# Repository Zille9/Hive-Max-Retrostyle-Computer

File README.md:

# Hive-Max-Retrostyle-Computer
umfangreich erweiterter Hive-Retrostyle-Computer

Folgende Änderungen wurden durchgeführt:
- 2xJoystick Ports (wie Mini-Joystickkarte)
- Bellatrix-Ram-Erweiterung integriert (für Emulatoren)
- Umschaltung Soundquelle von Administra nach Bellatrix (für Emulatoren)
- zusätzlicher Latchbaustein für die Aktivierung/Deaktivierung zusätzlicher Funktionen
- Portsperren am Bellatrix VGA-Ausgang, um die Ports für eigene Erweiterungen zu nutzen (andere Grafikhardware, CP/M-Emulation usw.)
- Möglichkeit der Anbindung des Micromite an den Hive
- Expansionsport als C64 Modulport ausgebildet für Hardware-Steckmodule
- automatische EEPROM-Umschaltung durch die Steckmodule über Adressumschaltung
- Latch-Diagnoseanschluss für den Zusatzlatch zur Funktionskontrolle

Für weitere Informationen siehe auch https://hive-project.de

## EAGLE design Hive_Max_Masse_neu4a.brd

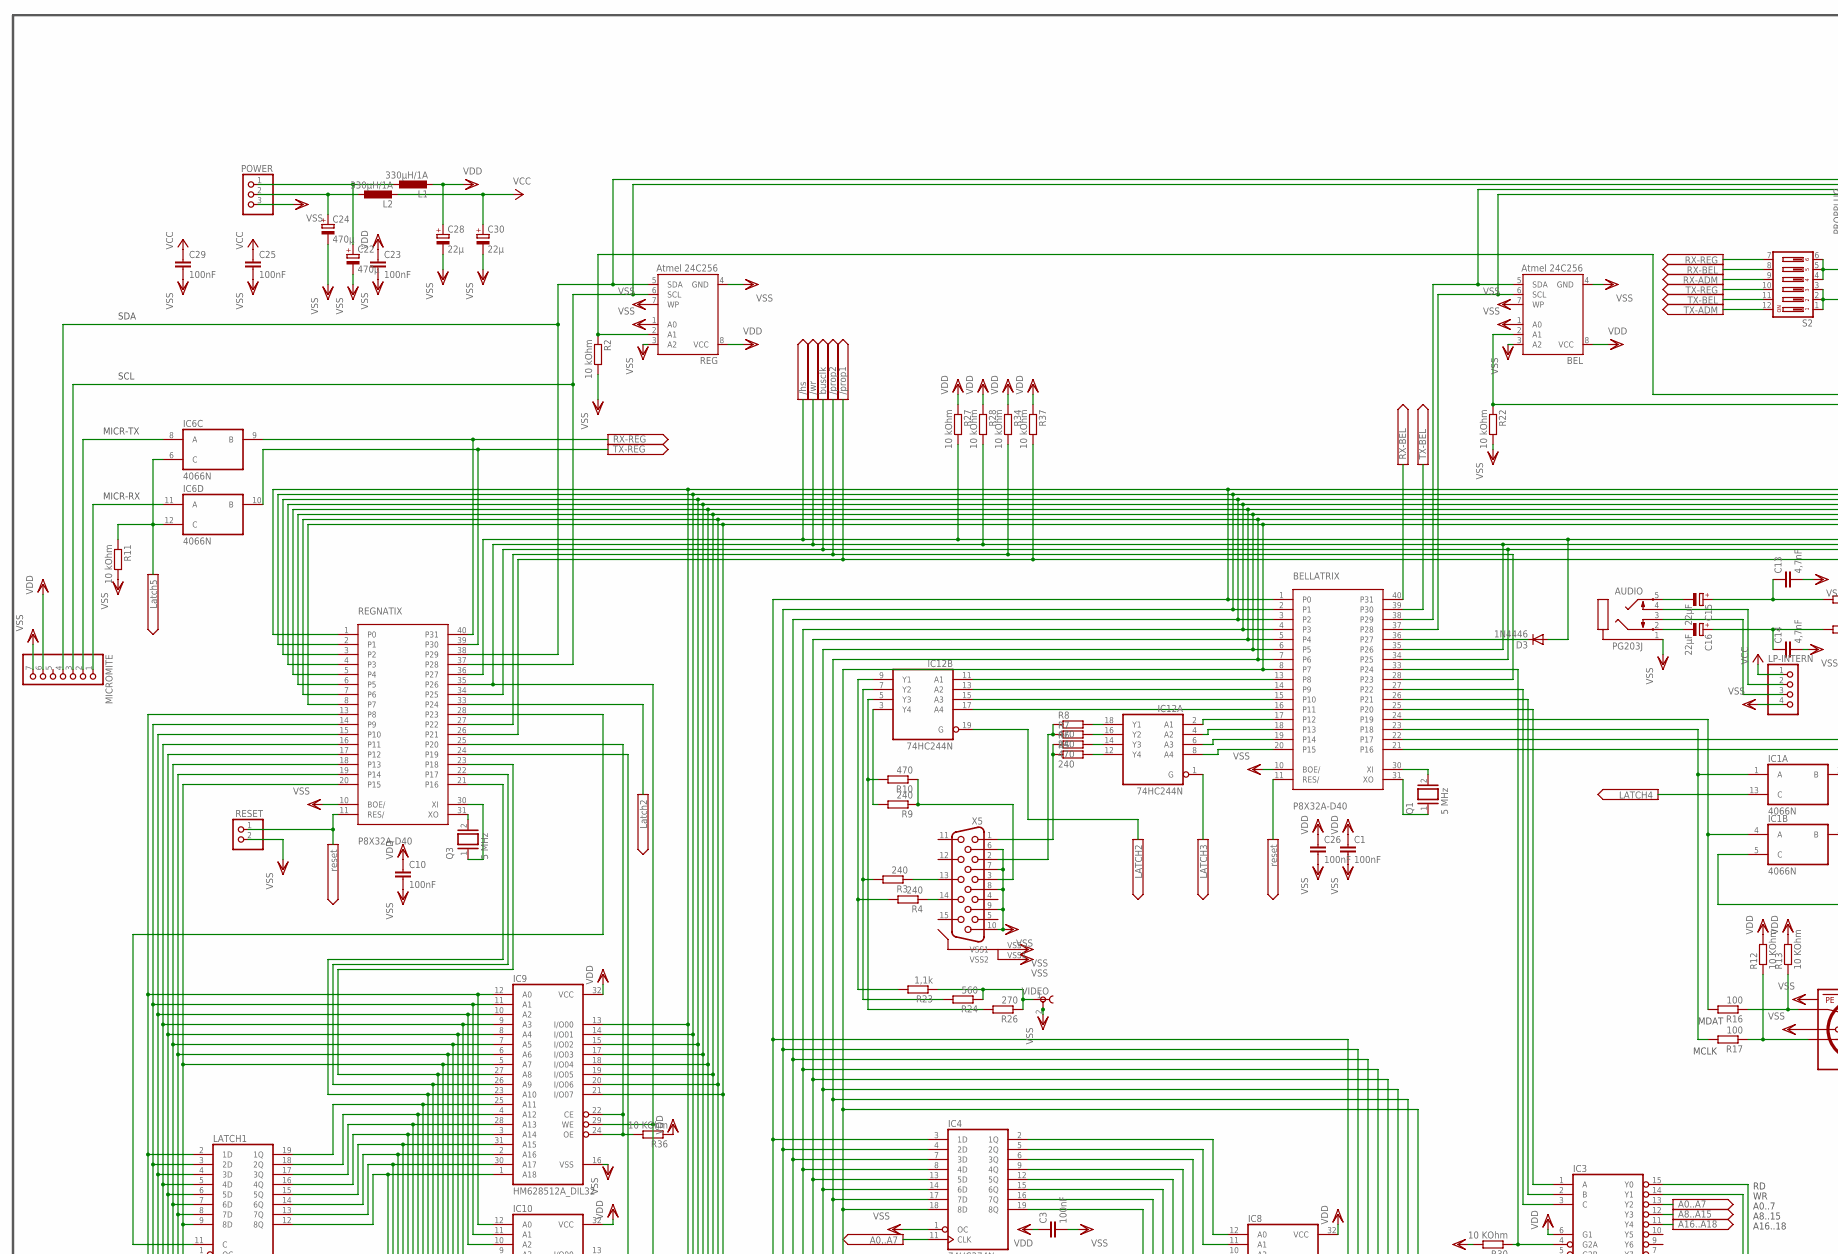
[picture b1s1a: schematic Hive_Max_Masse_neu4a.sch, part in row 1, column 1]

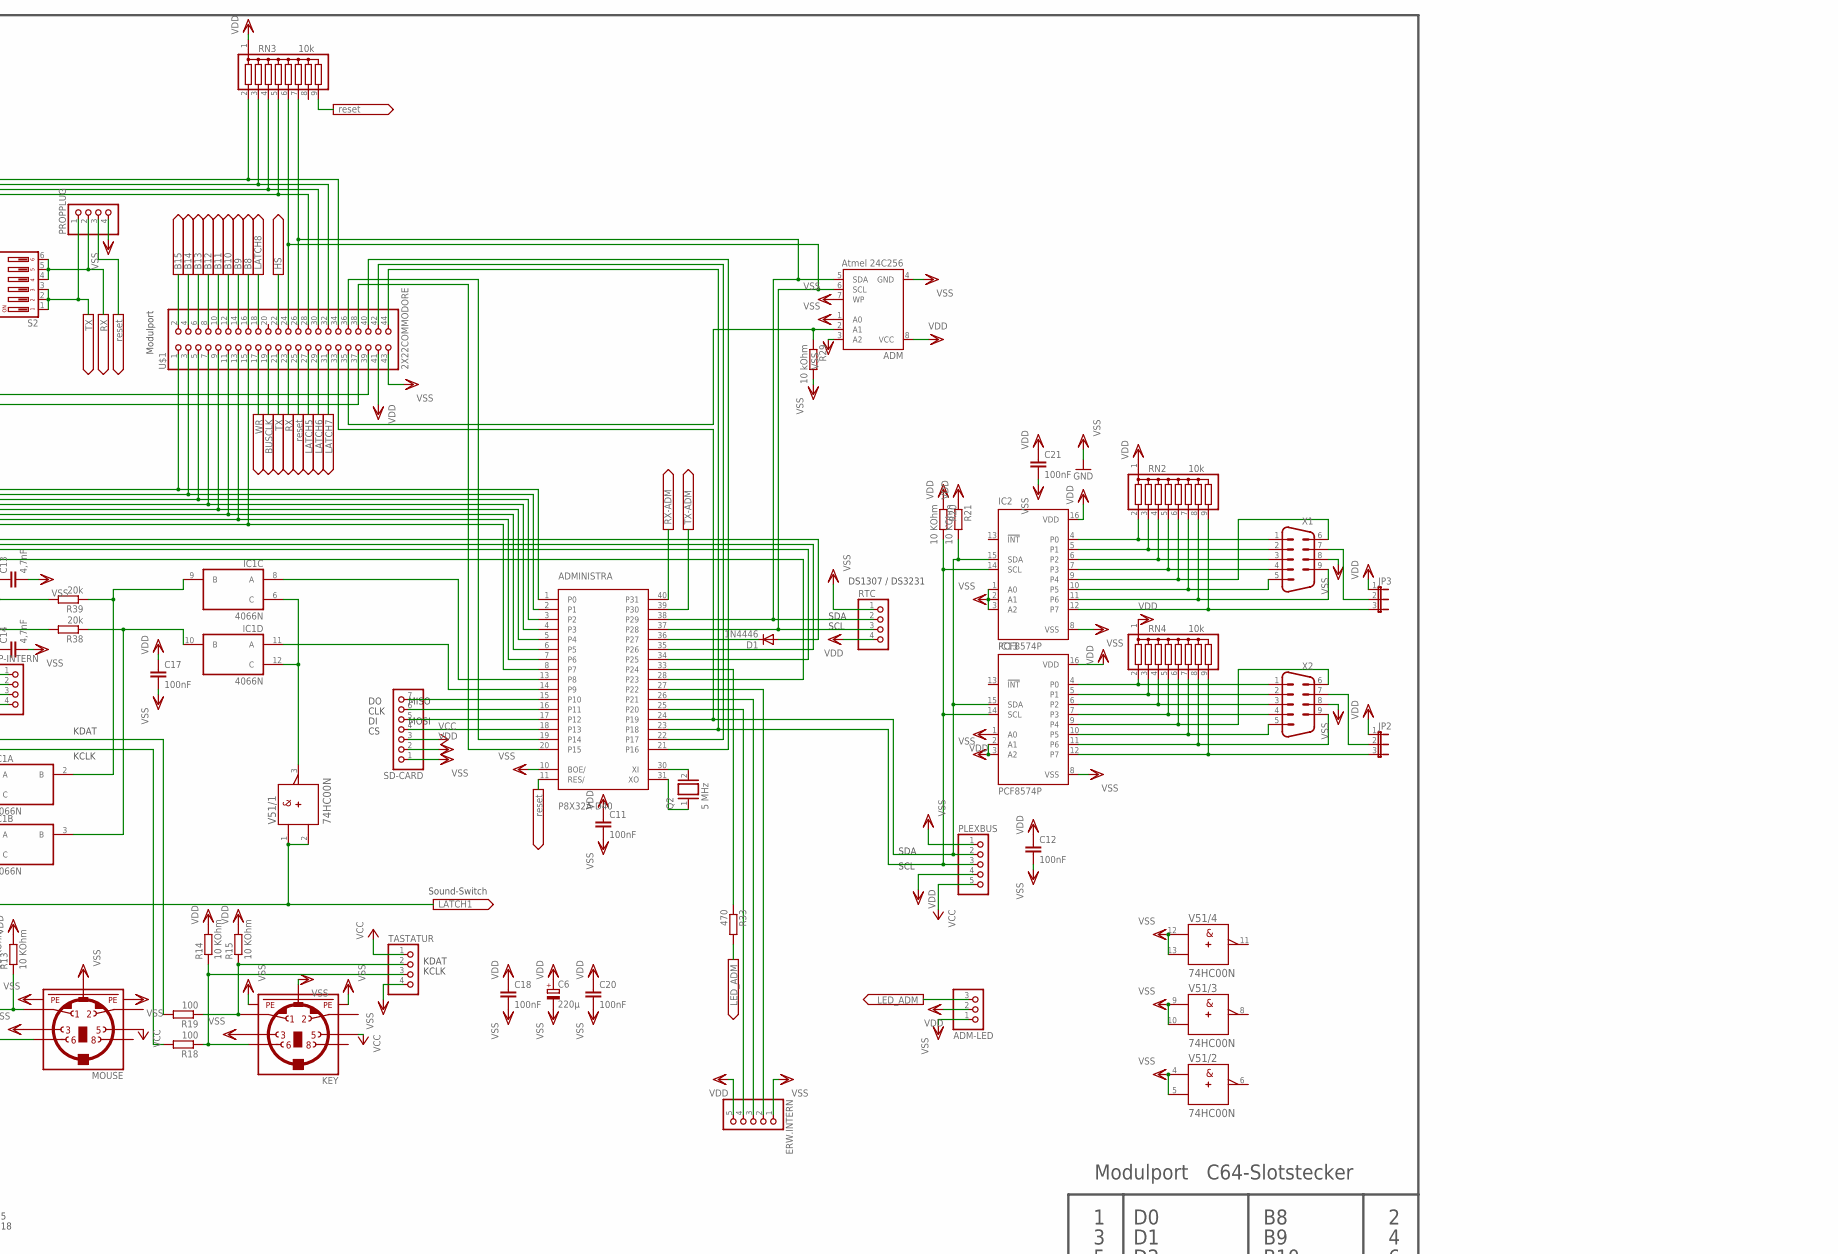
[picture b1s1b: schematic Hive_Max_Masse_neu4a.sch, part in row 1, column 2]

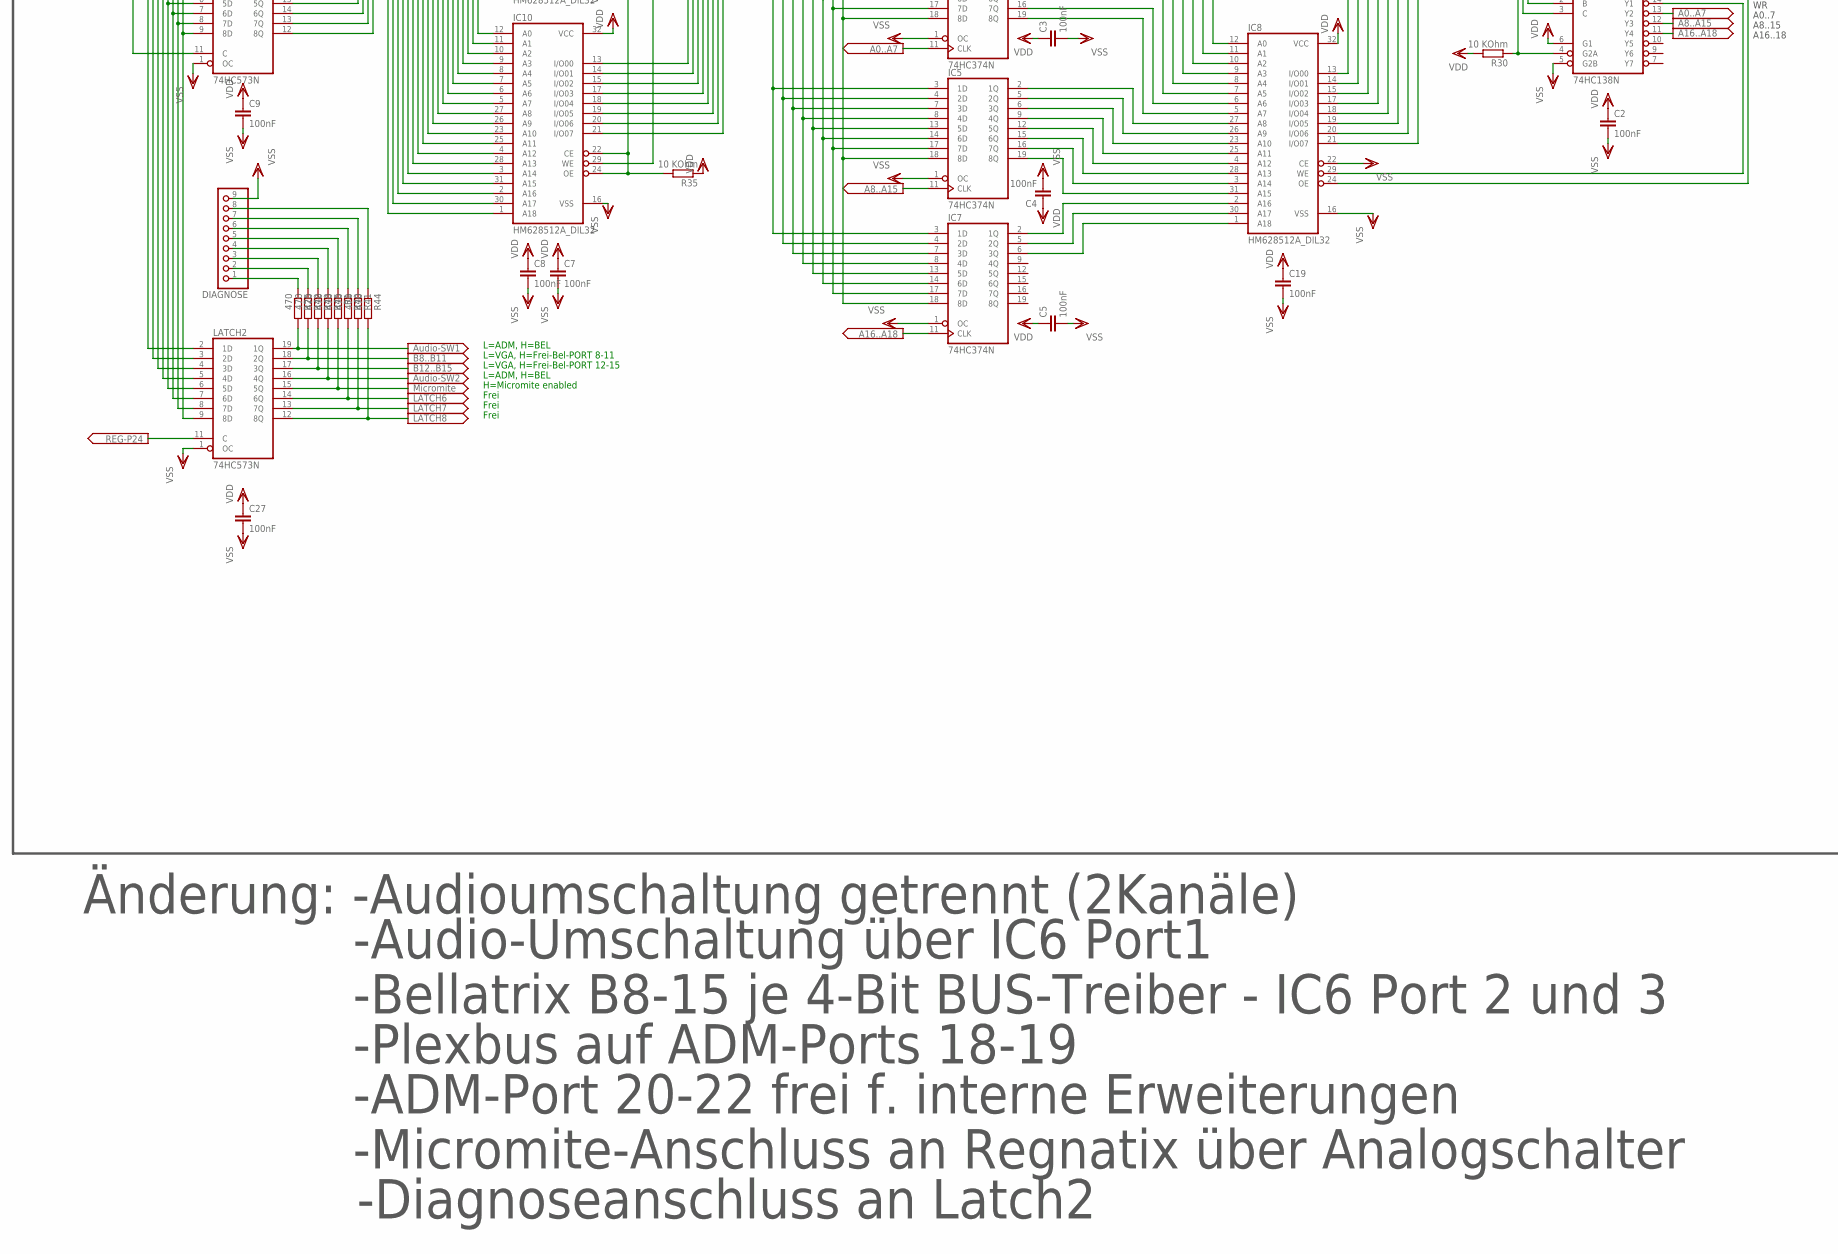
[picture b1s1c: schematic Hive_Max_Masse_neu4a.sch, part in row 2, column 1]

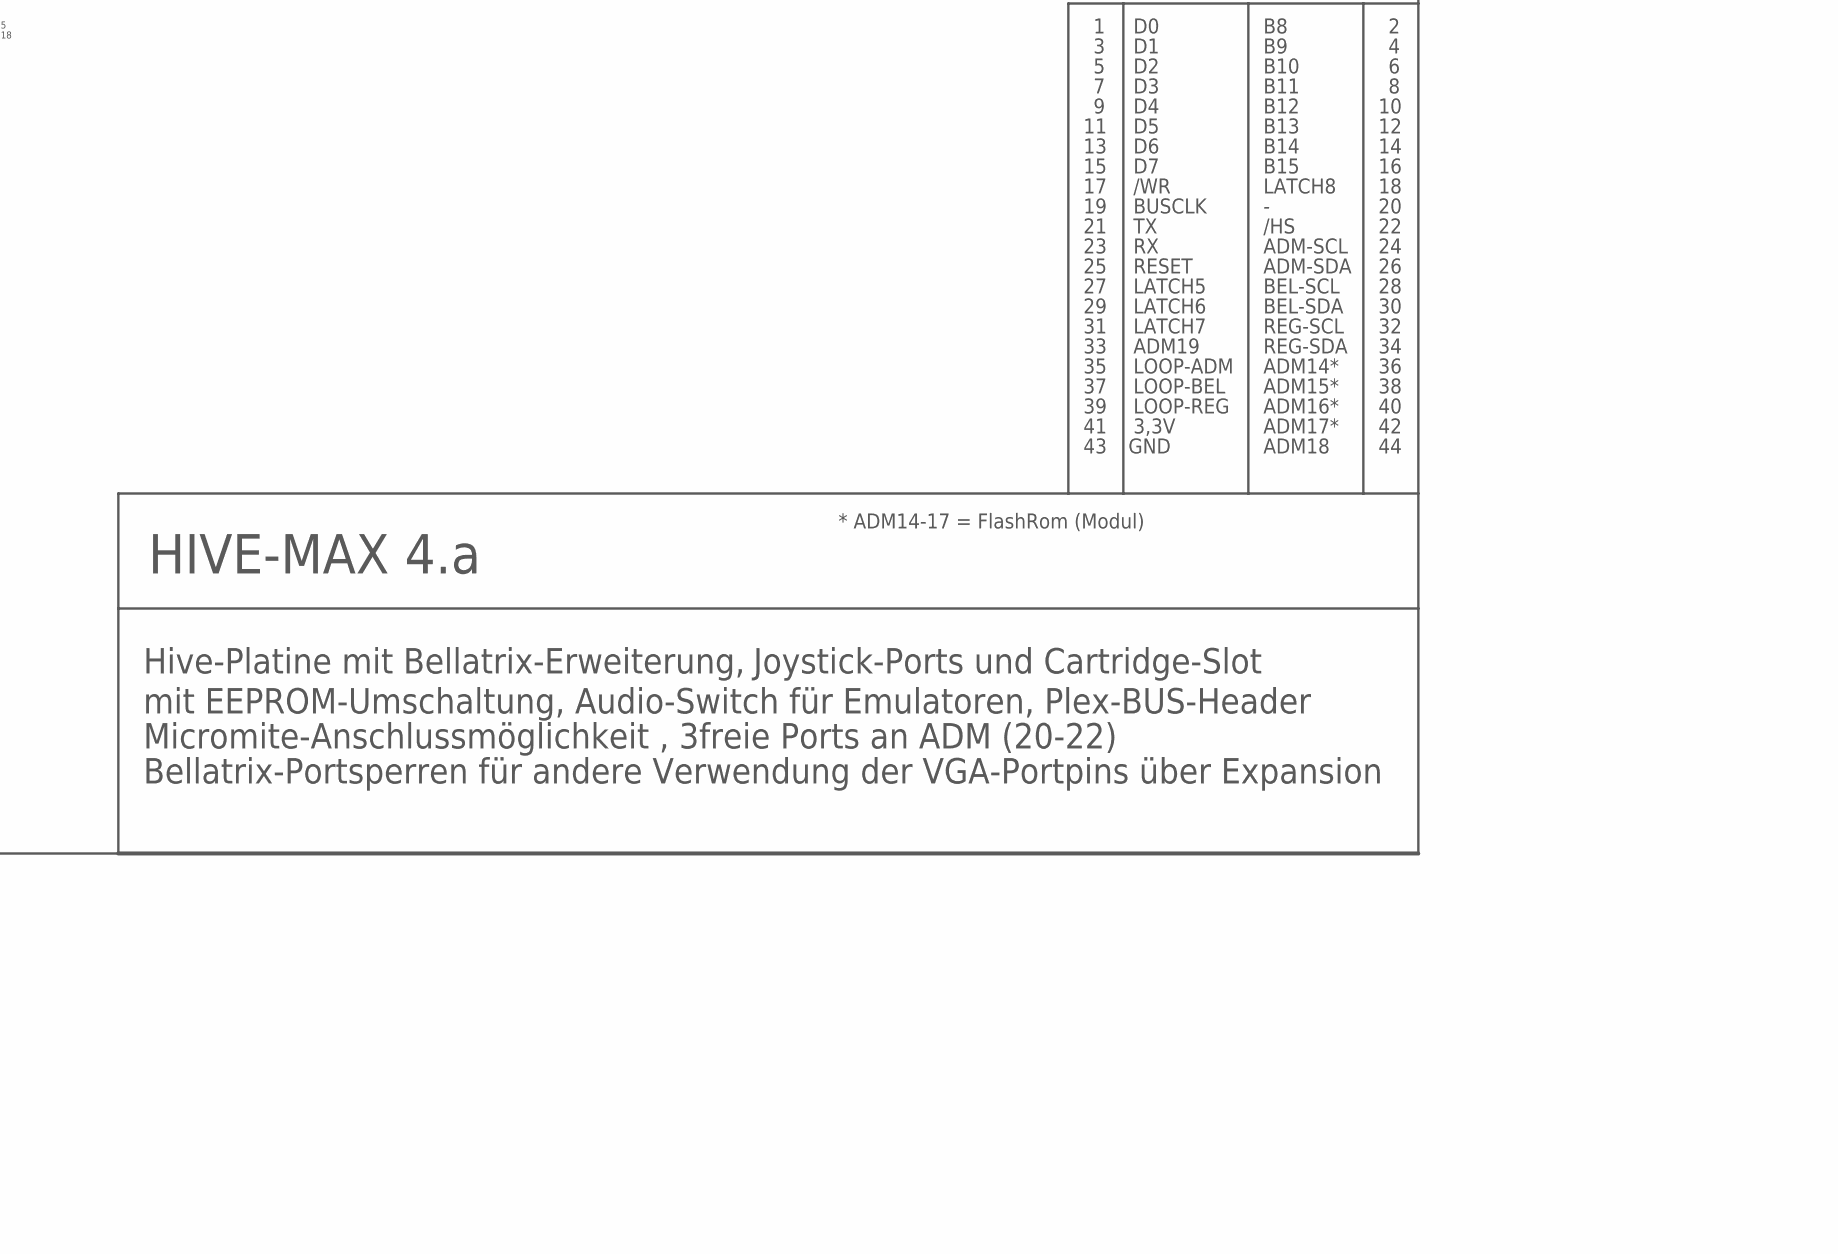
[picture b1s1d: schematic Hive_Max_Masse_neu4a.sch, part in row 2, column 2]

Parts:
ADM: Atmel 24C256; DIL08
ADM-LED: PINHD-1X3; 1X03
ADMINISTRA: P8X32A-D40
AUDIO: PG203J
BEL: Atmel 24C256; DIL08
BELLATRIX: P8X32A-D40
C1, C2, C3, C4, C5, C7, C8, C9, C10, C11, C12, C17, C18, C19, C20, C21, C23, C25, C26, C27, C29: 100nF; C025-030X050
C6: 220µ; E5-8,5
C13, C14: 4,7nF; C025-030X050
C15, C16: 22µF; E2-5
C22, C24: 470µ; E5-8,5
C28, C30: 22µ; E2-5
D1, D3: 1N4446; DO35-10
DIAGNOSE: PINHD-1X9; 1X09
ERW.INTERN: PINHD-1X5; 1X05
IC1, IC6: 4066N; DIL14
IC2, IC13: PCF8574P; DIL16
IC3: 74HC138N; DIL16
IC4, IC5, IC7: 74HC374N; DIL20
IC8, IC9, IC10: HM628512A_DIL32; DIL32
IC12: 74HC244N; DIL20
JP2, JP3: JP2E; JP2
KEY: MINI_DIN_6; M_DIN6
L1, L2: 330µH/1A; 6000-XXXX-RC
LATCH1, LATCH2: 74HC573N; DIL20
LP-INTERN: PINHD-1X4; 1X04
MICROMITE: PINHD-1X7; 1X07
MOUSE: MINI_DIN_6; M_DIN6
PLEXBUS: PINHD-1X5; 1X05
POWER: PINHD-1X3; 1X03
PROPPLUG: PINHD-1X4/90; 1X04/90
Q1, Q2, Q3: 5 MHz; QS
R1, R6, R8, R10, R25, R33, R40, R41, R42, R43, R44, R45: 470; 0204V
R2, R11, R22, R27, R28, R29, R34, R37: 10 kOhm; 0204V
R3, R4, R5, R7, R9: 240; 0204V
R12, R13, R14, R15, R20, R21, R30, R35, R36: 10 KOhm; 0204V
R16, R17, R18, R19: 100; 0204V
R23: 1,1k; 0204V
R24: 560; 0204V
R26: 270; 0204V
R38, R39: 20k; 0204V
REG: Atmel 24C256; DIL08
REGNATIX: P8X32A-D40
RESET: PINHD-1X2; 1X02
RN2, RN3, RN4: 10k; SIL9
RTC: PINHD-1X4; 1X04
S2: DA06; DA-06
SD-CARD: PINHD-1X7; 1X07
TASTATUR: PINHD-1X4; 1X04
U$1: 2X22COMMODORE; 2X22-COMMODORE
V51: 74HC00N; DIL14
VIDEO: CINCHFEM; TOBU3
X1, X2: M09HP
X5: HF15H; HDF15H

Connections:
/HS: D1.A, D3.A, R27.2, REGNATIX.36 (P27), U$1.22
A0: IC9.12 (A0), IC10.12 (A0), LATCH1.2 (1D), LATCH2.2 (1D), REGNATIX.13 (P8)
A0..A7: IC3.13 (Y2), IC4.11 (CLK)
A1: IC9.11 (A1), IC10.11 (A1), LATCH1.3 (2D), LATCH2.3 (2D), REGNATIX.14 (P9)
A2: IC9.10 (A2), IC10.10 (A2), LATCH1.4 (3D), LATCH2.4 (3D), REGNATIX.15 (P10)
A3: IC9.9 (A3), IC10.9 (A3), LATCH1.5 (4D), LATCH2.5 (4D), REGNATIX.16 (P11)
A4: IC9.8 (A4), IC10.8 (A4), LATCH1.6 (5D), LATCH2.6 (5D), REGNATIX.17 (P12)
A5: IC9.7 (A5), IC10.7 (A5), LATCH1.7 (6D), LATCH2.7 (6D), REGNATIX.18 (P13)
A6: IC9.6 (A6), IC10.6 (A6), LATCH1.8 (7D), LATCH2.8 (7D), REGNATIX.19 (P14)
A7: IC9.5 (A7), IC10.5 (A7), LATCH1.9 (8D), LATCH2.9 (8D), REGNATIX.20 (P15)
A8: IC9.23 (A10), IC10.23 (A10), REGNATIX.21 (P16)
A8..A15: IC3.12 (Y3), IC5.11 (CLK)
A9: IC9.26 (A9), IC10.26 (A9), REGNATIX.22 (P17)
A10: IC9.27 (A8), IC10.27 (A8), REGNATIX.23 (P18)
A16..A18: IC3.11 (Y4), IC7.11 (CLK)
ADM14: ADMINISTRA.19 (P14), U$1.36
ADM15: ADMINISTRA.20 (P15), U$1.38
ADM16: ADMINISTRA.21 (P16), U$1.40
ADM17: ADMINISTRA.22 (P17), U$1.42
ADM18: ADMINISTRA.23 (P18), IC2.14 (SCL), IC13.14 (SCL), PLEXBUS.3, R20.2, U$1.44
ADM19: ADMINISTRA.24 (P19), IC2.15 (SDA), IC13.15 (SDA), PLEXBUS.2, R21.2, U$1.33
ADM20: ADMINISTRA.25 (P20), ERW.INTERN.4
ADM21: ADMINISTRA.26 (P21), ERW.INTERN.3
ADM22: ADMINISTRA.27 (P22), ERW.INTERN.2
ADM-SCL: ADM.6 (SCL), ADMINISTRA.37 (P28), RN3.6, RTC.3, U$1.24
ADM-SDA: ADM.5 (SDA), ADMINISTRA.38 (P29), RN3.7, RTC.2, U$1.26
B8: BELLATRIX.13 (P8), IC12.11 (A1), U$1.16
B9: BELLATRIX.14 (P9), IC12.13 (A2), U$1.14
B10: BELLATRIX.15 (P10), IC12.15 (A3), U$1.12
B11: BELLATRIX.16 (P11), IC12.17 (A4), U$1.10
B12: BELLATRIX.17 (P12), IC12.2 (A1), U$1.8
B13: BELLATRIX.18 (P13), IC12.4 (A2), U$1.6
B14: BELLATRIX.19 (P14), IC12.6 (A3), U$1.4
B15: BELLATRIX.20 (P15), IC12.8 (A4), U$1.2
BEL-SCL: BEL.6 (SCL), BELLATRIX.37 (P28), RN3.5, U$1.28
BEL-SDA: BEL.5 (SDA), BELLATRIX.38 (P29), RN3.4, U$1.30
BLAU: R9.1, R10.1, X5.3
BUSCLK: ADMINISTRA.34 (P25), BELLATRIX.34 (P25), REGNATIX.34 (P25), U$1.19
CLK: KEY.6, R14.1, R18.1, TASTATUR.3
D0: ADMINISTRA.1 (P0), BELLATRIX.1 (P0), IC4.3 (1D), IC5.3 (1D), IC7.3 (1D), IC8.13 (I/O00), IC9.13 (I/O00), IC10.13 (I/O00), REGNATIX.1 (P0), U$1.1
D1: ADMINISTRA.2 (P1), BELLATRIX.2 (P1), IC4.4 (2D), IC5.4 (2D), IC7.4 (2D), IC8.14 (I/O01), IC9.14 (I/O01), IC10.14 (I/O01), REGNATIX.2 (P1), U$1.3
D2: ADMINISTRA.3 (P2), BELLATRIX.3 (P2), IC4.7 (3D), IC5.7 (3D), IC7.7 (3D), IC8.15 (I/O02), IC9.15 (I/O02), IC10.15 (I/O02), REGNATIX.3 (P2), U$1.5
D3: ADMINISTRA.4 (P3), BELLATRIX.4 (P3), IC4.8 (4D), IC5.8 (4D), IC7.8 (4D), IC8.17 (I/O03), IC9.17 (I/O03), IC10.17 (I/O03), REGNATIX.4 (P3), U$1.7
D4: ADMINISTRA.5 (P4), BELLATRIX.5 (P4), IC4.13 (5D), IC5.13 (5D), IC7.13 (5D), IC8.18 (I/O04), IC9.18 (I/O04), IC10.18 (I/O04), REGNATIX.5 (P4), U$1.9
D5: ADMINISTRA.6 (P5), BELLATRIX.6 (P5), IC4.14 (6D), IC5.14 (6D), IC7.14 (6D), IC8.19 (I/O05), IC9.19 (I/O05), IC10.19 (I/O05), REGNATIX.6 (P5), U$1.11
D6: ADMINISTRA.7 (P6), BELLATRIX.7 (P6), IC4.17 (7D), IC5.17 (7D), IC7.17 (7D), IC8.20 (I/O06), IC9.20 (I/O06), IC10.20 (I/O06), REGNATIX.7 (P6), U$1.13
D7: ADMINISTRA.8 (P7), BELLATRIX.8 (P7), IC4.18 (8D), IC5.18 (8D), IC7.18 (8D), IC8.21 (I/O07), IC9.21 (I/O07), IC10.21 (I/O07), REGNATIX.8 (P7), U$1.15
DAT: KEY.1, R15.1, R19.1, TASTATUR.2
GLOB_RESET: ADMINISTRA.11 (RES/), BELLATRIX.11 (RES/), PROPPLUG.3, REGNATIX.11 (RES/), RESET.1, RN3.9, U$1.25
GRUEN: R7.1, R8.1, X5.2
HSYNC: R3.1, X5.13
KCLK: BELLATRIX.21 (P16), R18.2
KDAT: BELLATRIX.22 (P17), R19.2
LATCH1: IC1.5 (C), LATCH2.19 (1Q), R25.2, V51.1 (A), V51.2 (B)
LATCH2: IC12.19 (G), LATCH2.18 (2Q), R42.2
LATCH3: IC12.1 (G), LATCH2.17 (3Q), R43.2
LATCH4: IC1.13 (C), LATCH2.16 (4Q), R45.2
LATCH5: IC6.6 (C), IC6.12 (C), LATCH2.15 (5Q), R1.2, R11.1, U$1.27
LATCH6: LATCH2.14 (6Q), R40.2, U$1.29
LATCH7: LATCH2.13 (7Q), R41.2, U$1.31
LATCH8: LATCH2.12 (8Q), R44.2, U$1.18
LED_ADM: ADM-LED.3, R33.2
LOOP-ADM: ADM.2 (A1), R29.1, U$1.35
LOOP-BEL: BEL.2 (A1), R22.1, U$1.37
LOOP-REG: R2.1, REG.2 (A1), U$1.39
MCLK: BELLATRIX.23 (P18), IC1.1 (A), R17.2
MDAT: BELLATRIX.24 (P19), IC1.4 (A), R16.2
unnamed: AUDIO.4, LP-INTERN.2
unnamed: AUDIO.3, LP-INTERN.3
unnamed: ADMINISTRA.14 (P9), IC1.11 (A)
unnamed: DIAGNOSE.1, R25.1
unnamed: IC12.18 (Y1), R8.2
unnamed: IC6.11 (A), MICROMITE.1
unnamed: DIAGNOSE.2, R42.1
unnamed: IC12.16 (Y2), R7.2
unnamed: IC12.14 (Y3), R6.2
unnamed: C22.+, L1.1, POWER.1
unnamed: C24.+, L2.1, POWER.2
unnamed: IC12.12 (Y4), R5.2
unnamed: IC6.8 (A), MICROMITE.2
unnamed: IC12.9 (Y1), R4.2, R23.2
unnamed: IC12.7 (Y2), R3.2, R24.2
unnamed: ADMINISTRA.30 (XI), Q2.2
unnamed: IC4.2 (1Q), IC8.12 (A0)
unnamed: IC4.5 (2Q), IC8.11 (A1)
unnamed: IC4.6 (3Q), IC8.10 (A2)
unnamed: IC4.9 (4Q), IC8.9 (A3)
unnamed: IC4.12 (5Q), IC8.8 (A4)
unnamed: IC12.5 (Y3), R10.2, R26.2
unnamed: DIAGNOSE.3, R43.1
unnamed: DIAGNOSE.4, R45.1
unnamed: DIAGNOSE.5, R1.1
unnamed: IC1.3 (B), IC1.10 (B), R38.1
unnamed: IC1.6 (C), IC1.12 (C), V51.3 (Y)
unnamed: IC12.3 (Y4), R9.2
unnamed: DIAGNOSE.6, R40.1
unnamed: DIAGNOSE.7, R41.1
unnamed: DIAGNOSE.8, R44.1
unnamed: BELLATRIX.30 (XI), Q1.2
unnamed: BELLATRIX.31 (XO), Q1.1
unnamed: BELLATRIX.36 (P27), D3.C
unnamed: IC1.2 (B), IC1.9 (B), R39.1
unnamed: MOUSE.1, R13.1, R16.1
unnamed: MOUSE.6, R12.1, R17.1
unnamed: ADMINISTRA.33 (P24), R33.1
unnamed: IC4.15 (6Q), IC8.7 (A5)
unnamed: IC4.16 (7Q), IC8.6 (A6)
unnamed: IC4.19 (8Q), IC8.5 (A7)
unnamed: R23.1, R24.1, R26.1, VIDEO.1
unnamed: ADMINISTRA.31 (XO), Q2.1
unnamed: IC5.2 (1Q), IC8.27 (A8)
unnamed: ADMINISTRA.15 (P10), SD-CARD.7
unnamed: ADMINISTRA.16 (P11), SD-CARD.6
unnamed: ADMINISTRA.17 (P12), SD-CARD.5
unnamed: ADMINISTRA.36 (P27), D1.C
unnamed: ADMINISTRA.18 (P13), SD-CARD.4
unnamed: Q3.2, REGNATIX.31 (XO)
unnamed: Q3.1, REGNATIX.30 (XI)
unnamed: IC2.7 (P3), RN2.5, X1.4
unnamed: IC2.4 (P0), RN2.2, X1.1
unnamed: IC5.5 (2Q), IC8.26 (A9)
unnamed: IC5.6 (3Q), IC8.23 (A10)
unnamed: IC5.9 (4Q), IC8.25 (A11)
unnamed: IC5.12 (5Q), IC8.4 (A12)
unnamed: IC5.15 (6Q), IC8.28 (A13)
unnamed: IC5.16 (7Q), IC8.3 (A14)
unnamed: IC5.19 (8Q), IC8.31 (A15)
unnamed: IC7.2 (1Q), IC8.2 (A16)
unnamed: IC7.5 (2Q), IC8.30 (A17)
unnamed: IC7.6 (3Q), IC8.1 (A18)
unnamed: IC9.25 (A11), IC10.25 (A11), LATCH1.19 (1Q)
unnamed: IC9.4 (A12), IC10.4 (A12), LATCH1.18 (2Q)
unnamed: IC9.28 (A13), IC10.28 (A13), LATCH1.17 (3Q)
unnamed: IC9.3 (A14), IC10.3 (A14), LATCH1.16 (4Q)
unnamed: IC9.31 (A15), IC10.31 (A15), LATCH1.15 (5Q)
unnamed: IC9.2 (A16), IC10.2 (A16), LATCH1.14 (6Q)
unnamed: IC9.30 (A17), IC10.30 (A17), LATCH1.13 (7Q)
unnamed: IC9.1 (A18), IC10.1 (A18), LATCH1.12 (8Q)
unnamed: LATCH1.11 (C), REGNATIX.28 (P23)
unnamed: IC2.5 (P1), RN2.3, X1.2
unnamed: IC2.6 (P2), RN2.4, X1.3
unnamed: IC13.7 (P3), RN4.5, X2.4
unnamed: IC13.9 (P4), RN4.6, X2.6
unnamed: IC2.10 (P5), RN2.7, X1.5
unnamed: IC2.9 (P4), RN2.6, X1.6
unnamed: IC2.12 (P7), JP3.3, RN2.9
unnamed: IC13.4 (P0), RN4.2, X2.1
unnamed: IC13.5 (P1), RN4.3, X2.2
unnamed: IC13.6 (P2), RN4.4, X2.3
unnamed: IC13.11 (P6), RN4.8, X2.9
unnamed: IC2.11 (P6), RN2.8, X1.9
unnamed: IC13.10 (P5), RN4.7, X2.5
unnamed: JP2.2, X2.7
unnamed: IC13.12 (P7), JP2.3, RN4.9
unnamed: JP3.2, X1.7
unnamed: ADMINISTRA.13 (P8), IC1.8 (A)
unnamed: AUDIO.2, C16.-
unnamed: AUDIO.5, C15.-
unnamed: C13.1, C15.+, R39.2
unnamed: C14.1, C16.+, R38.2
PROP1: ADMINISTRA.28 (P23), R37.2, REGNATIX.26 (P21)
PROP2: BELLATRIX.28 (P23), R34.2, REGNATIX.27 (P22)
RAM1: IC10.22 (CE), IC10.24 (OE), R35.2, REGNATIX.24 (P19)
RAM2: IC9.22 (CE), IC9.24 (OE), R36.2, REGNATIX.25 (P20)
RAM-RD: IC3.15 (Y0), IC8.24 (OE)
RAM-WR: IC3.14 (Y1), IC8.29 (WE)
REG-P24: LATCH2.11 (C), REGNATIX.33 (P24)
REG-SCL: MICROMITE.3, REG.6 (SCL), REGNATIX.37 (P28), RN3.3, U$1.32
REG-SDA: MICROMITE.4, REG.5 (SDA), REGNATIX.38 (P29), RN3.2, U$1.34
ROT: R5.1, R6.1, X5.1
RX: PROPPLUG.2, S2.4, S2.5, S2.6, U$1.23
RX-ADM: ADMINISTRA.40 (P31), S2.9
RX-BEL: BELLATRIX.40 (P31), S2.8
RX-REG: IC6.9 (B), REGNATIX.40 (P31), S2.7
TX: PROPPLUG.1, S2.1, S2.2, S2.3, U$1.21
TX-ADM: ADMINISTRA.39 (P30), S2.12
TX-BEL: BELLATRIX.39 (P30), S2.11
TX-REG: IC6.10 (B), REGNATIX.39 (P30), S2.10
VCC: C25.1, C29.1, C30.+, KEY.5, L2.2, LP-INTERN.1, MOUSE.5, PLEXBUS.5, SD-CARD.3, TASTATUR.1
VDD: ADM.8 (VCC), ADM-LED.2, ADMINISTRA.12 (VDD), ADMINISTRA.32 (VDD), BEL.8 (VCC), BELLATRIX.12 (VDD), BELLATRIX.32 (VDD), C1.1, C2.1, C3.1, C4.1, C5.1, C6.+, C7.1, C8.1, C9.1, C10.1, C11.1, C12.1, C17.1, C18.1, C19.1, C20.1, C21.1, C23.1, C26.1, C27.1, C28.+, ERW.INTERN.5, IC1.14 (VDD), IC2.16 (VDD), IC3.6 (G1), IC3.16 (VDD), IC4.20 (VDD), IC5.20 (VDD), IC6.14 (VDD), IC7.20 (VDD), IC8.32 (VCC), IC9.32 (VCC), IC10.32 (VCC), IC12.20 (VDD), IC13.1 (A0), IC13.16 (VDD), JP2.1, JP3.1, L1.2, LATCH1.20 (VDD), LATCH2.20 (VDD), MICROMITE.6, PLEXBUS.4, R12.2, R13.2, R14.2, R15.2, R20.1, R21.1, R27.1, R28.1, R30.2, R34.1, R35.1, R36.1, R37.1, REG.8 (VCC), REGNATIX.12 (VDD), REGNATIX.32 (VDD), RN2.1, RN3.1, RN4.1, RTC.4, SD-CARD.2, U$1.41, V51.14 (VDD)
VSS: ADM.1 (A0), ADM.3 (A2), ADM.4 (GND), ADM.7 (WP), ADM-LED.1, ADMINISTRA.9 (GND), ADMINISTRA.10 (BOE/), ADMINISTRA.29 (GND), AUDIO.1, BEL.1 (A0), BEL.3 (A2), BEL.4 (GND), BEL.7 (WP), BELLATRIX.9 (GND), BELLATRIX.10 (BOE/), BELLATRIX.29 (GND), C1.2, C2.2, C3.2, C4.2, C5.2, C6.-, C7.2, C8.2, C9.2, C10.2, C11.2, C12.2, C13.2, C14.2, C17.2, C18.2, C19.2, C20.2, C21.2, C22.-, C23.2, C24.-, C25.2, C26.2, C27.2, C28.-, C29.2, C30.-, DIAGNOSE.9, ERW.INTERN.1, IC1.7 (VSS), IC2.1 (A0), IC2.2 (A1), IC2.3 (A2), IC2.8 (VSS), IC3.5 (G2B), IC3.8 (GND), IC4.1 (OC), IC4.10 (GND), IC5.1 (OC), IC5.10 (GND), IC6.7 (VSS), IC7.1 (OC), IC7.10 (GND), IC8.16 (VSS), IC8.22 (CE), IC9.16 (VSS), IC10.16 (VSS), IC12.10 (GND), IC13.2 (A1), IC13.3 (A2), IC13.8 (VSS), KEY.3, KEY.SH1 (PE1), KEY.SH2 (PE2), KEY.SH3 (PE3), LATCH1.1 (OC), LATCH1.10 (GND), LATCH2.1 (OC), LATCH2.10 (GND), LP-INTERN.4, MICROMITE.7, MOUSE.3, MOUSE.SH1 (PE1), MOUSE.SH2 (PE2), MOUSE.SH3 (PE3), PLEXBUS.1, POWER.3, PROPPLUG.4, R2.2, R11.2, R22.2, R29.2, REG.1 (A0), REG.3 (A2), REG.4 (GND), REG.7 (WP), REGNATIX.9 (GND), REGNATIX.10 (BOE/), REGNATIX.29 (GND), RESET.2, RTC.1, SD-CARD.1, TASTATUR.4, U$1.43, V51.4 (A), V51.5 (B), V51.7 (VSS), V51.9 (A), V51.10 (B), V51.12 (A), V51.13 (B), VIDEO.2, VIDEO.2@1 (3), VIDEO.2@2 (4), X1.8, X2.8, X5.6, X5.7, X5.8, X5.9, X5.10, X5.VSS (VSS1), X5.VSS1 (VSS2)
VSYNC: R4.1, X5.14
WR: ADMINISTRA.35 (P26), BELLATRIX.35 (P26), IC9.29 (WE), IC10.29 (WE), R28.2, REGNATIX.35 (P26), U$1.17
Y1: BELLATRIX.25 (P20), IC3.1 (A)
Y2: BELLATRIX.26 (P21), IC3.2 (B)
Y3: BELLATRIX.27 (P22), IC3.3 (C)
Y4: BELLATRIX.33 (P24), IC3.4 (G2A), R30.1

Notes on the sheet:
B10
B13
LATCH8
GND
3,3V
B11
B12
B14
B15
/HS
REG-SCL
BEL-SDA
BEL-SCL
ADM-SDA
ADM-SCL
/WR
BUSCLK
REG-SDA
ADM14*
ADM15*
ADM16*
ADM17*
ADM18
RESET
MCLK
MDAT
KDAT
KCLK
A0..7
A8..15
A16..18
CLK
Modulport
DS1307 / DS3231
HIVE-MAX 4.a
Hive-Platine mit Bellatrix-Erweiterung,
Joystick-Ports und Cartridge-Slot
mit EEPROM-Umschaltung, Audio-Switch für Emulatoren, Plex-BUS-Header
LATCH5
LATCH6

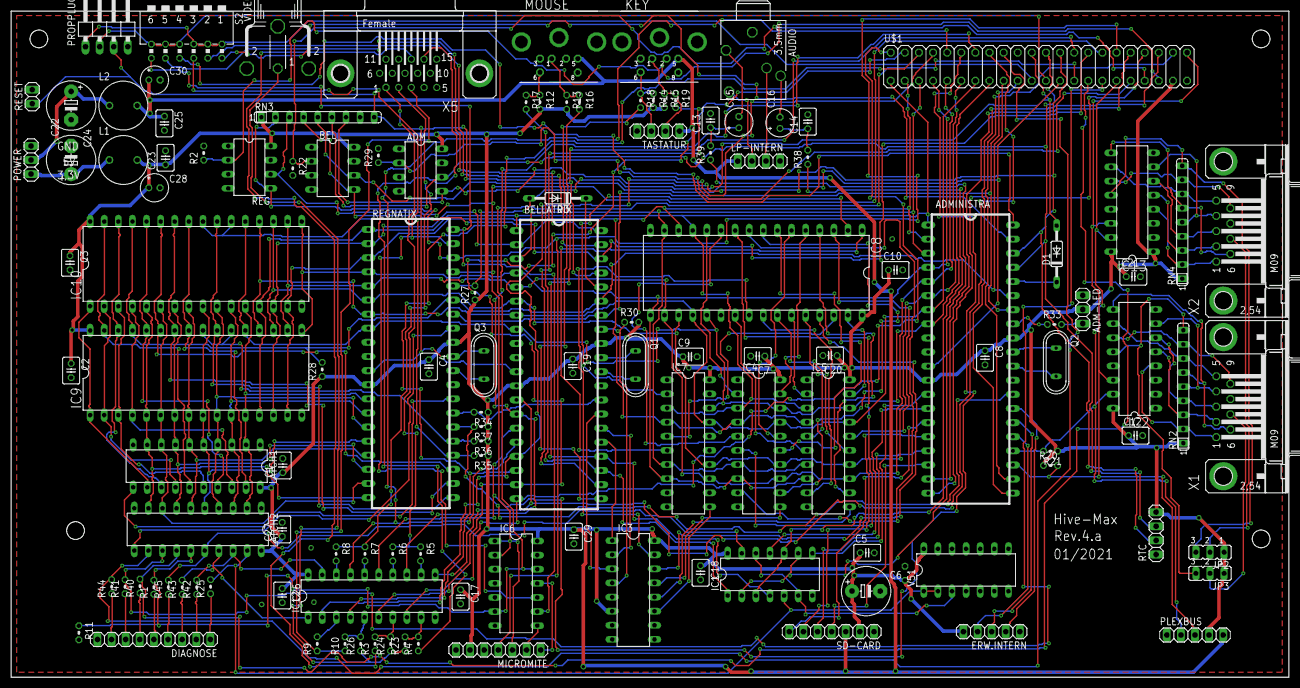
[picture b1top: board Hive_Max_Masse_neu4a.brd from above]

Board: 2 copper layers, 230.0 x 119.9 mm, 127 parts (1 on the bottom side), 187 nets.

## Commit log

2021-02-16 Hardware
2021-04-01 Pictures
2021-04-01 Größenkorrektur
